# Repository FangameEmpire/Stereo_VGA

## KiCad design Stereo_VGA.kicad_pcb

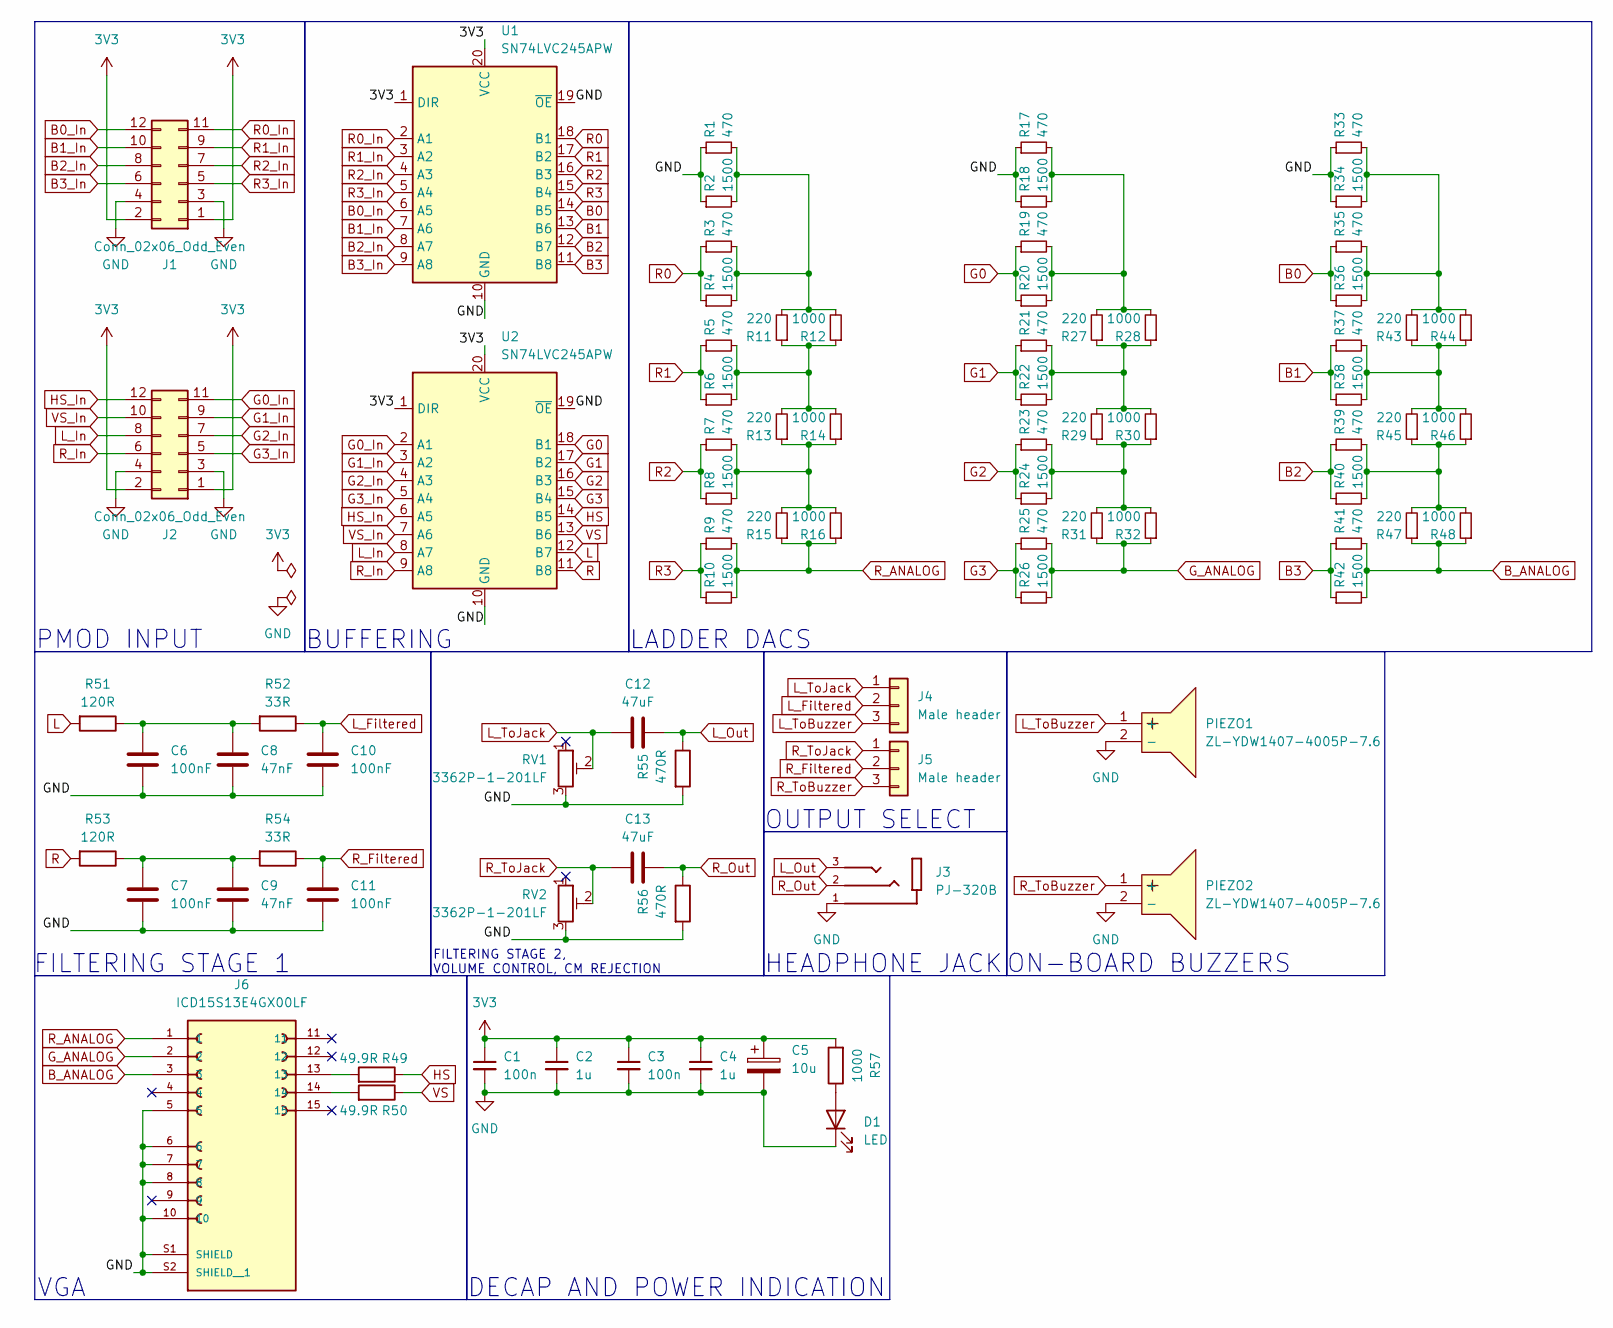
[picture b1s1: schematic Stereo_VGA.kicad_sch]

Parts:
C1, C3: 100n; C_0603_1608Metric; MPN CGA3E3X7S2A104M080AB
C2, C4: 1u; C_0603_1608Metric; MPN CGA3E3X7S2A104M080AB
C5: 10u; CP_Radial_D5.0mm_P2.50mm
C6, C7, C10, C11: 100nF; C_0603_1608Metric; LCSC Part C14663
C8, C9: 47nF; C_0603_1608Metric; LCSC Part C1622
C12, C13: 47uF; C_0603_1608Metric; LCSC Part C16780
D1: LED; LED_0603_1608Metric
J1, J2: Conn_02x06_Odd_Even; PinHeader_2x06_P2.54mm_Horizontal
J3: PJ-320B; BOOMELE_PJ-320B; LCSC Part C2884998
J4, J5: Male header; PinHeader_1x03_P2.54mm_Vertical; LCSC Part C49257
J6: ICD15S13E4GX00LF; AMPHENOL_ICD15S13E4GX00LF; PARTREV G
PIEZO1, PIEZO2: ZL-YDW1407-4005P-7.6; BUZ-TH_BD14.0-P7.60-D0.7-FD; LCSC Part C219740
R1, R3, R5, R7, R9, R17, R19, R21, R23, R25, R33, R35, R37, R39, R41: 470; R_0402_1005Metric; MPN RCC04021K50FKED
R2, R4, R6, R8, R10, R18, R20, R22, R24, R26, R34, R36, R38, R40, R42: 1500; R_0402_1005Metric; MPN RCC04021K50FKED
R11, R13, R15, R27, R29, R31, R43, R45, R47: 220; R_0402_1005Metric; MPN RCC04021K50FKED
R12, R14, R16, R28, R30, R32, R44, R46, R48: 1000; R_0402_1005Metric; MPN RCC04021K50FKED
R49, R50: 49.9R; R_0402_1005Metric; MPN ERJ-2RKF49R9X
R51, R53: 120R; R_0603_1608Metric; LCSC Part C22787
R52, R54: 33R; R_0603_1608Metric; LCSC Part C23140
R55, R56: 470R; R_0603_1608Metric; LCSC Part C23179
R57: 1000; R_0603_1608Metric; LCSC Part C23140
RV1, RV2: 3362P-1-201LF; TRIM_3362P-1-102; LCSC Part C124581
U1, U2: SN74LVC245APW; TSSOP-20_4.4x6.5mm_P0.65mm

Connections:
3V3: C1.1, C2.1, C3.1, C4.1, C5.1, J1.1, J1.2, J2.1, J2.2, R57.2, U1.1 (DIR), U1.20 (VCC), U2.1 (DIR), U2.20 (VCC)
B0: R35.1, R36.1, U1.14 (B5)
B0_In: J1.12, U1.6 (A5)
B1: R37.1, R38.1, U1.13 (B6)
B1_In: J1.10, U1.7 (A6)
B2: R39.1, R40.1, U1.12 (B7)
B2_In: J1.8, U1.8 (A7)
B3: R41.1, R42.1, U1.11 (B8)
B3_In: J1.6, U1.9 (A8)
B_ANALOG: J6.3, R41.2, R42.2, R47.1, R48.1
G0: R19.1, R20.1, U2.18 (B1)
G0_In: J2.11, U2.2 (A1)
G1: R21.1, R22.1, U2.17 (B2)
G1_In: J2.9, U2.3 (A2)
G2: R23.1, R24.1, U2.16 (B3)
G2_In: J2.7, U2.4 (A3)
G3: R25.1, R26.1, U2.15 (B4)
G3_In: J2.5, U2.5 (A4)
GND: C1.2, C2.2, C3.2, C4.2, C5.2, C6.2, C7.2, C8.2, C9.2, C10.2, C11.2, D1.1 (K), J1.3, J1.4, J2.3, J2.4, J3.1, J6.5, J6.6, J6.7, J6.8, J6.10, J6.S1 (SHIELD), J6.S2 (SHIELD__1), PIEZO1.2 (-), PIEZO2.2 (-), R1.1, R2.1, R17.1, R18.1, R33.1, R34.1, R55.2, R56.2, RV1.3, RV2.3, U1.10 (GND), U1.19 (~OE), U2.10 (GND), U2.19 (~OE)
G_ANALOG: J6.2, R25.2, R26.2, R31.1, R32.1
HS: R49.1, U2.14 (B5)
HS_In: J2.12, U2.6 (A5)
L: R51.2, U2.12 (B7)
L_Filtered: C10.1, J4.2, R52.1
L_In: J2.8, U2.8 (A7)
L_Out: C12.1, J3.3, R55.1
L_ToBuzzer: J4.3, PIEZO1.1 (+)
L_ToJack: C12.2, J4.1, RV1.2
unnamed: C6.1, C8.1, R51.1, R52.2
unnamed: C7.1, C9.1, R53.1, R54.2
unnamed: D1.2 (A), R57.1
unnamed: J6.13, R49.2
unnamed: J6.14, R50.2
unnamed: R1.2, R2.2, R3.2, R4.2, R11.2, R12.2
unnamed: R5.2, R6.2, R11.1, R12.1, R13.2, R14.2
unnamed: R7.2, R8.2, R13.1, R14.1, R15.2, R16.2
unnamed: R17.2, R18.2, R19.2, R20.2, R27.2, R28.2
unnamed: R21.2, R22.2, R27.1, R28.1, R29.2, R30.2
unnamed: R23.2, R24.2, R29.1, R30.1, R31.2, R32.2
unnamed: R33.2, R34.2, R35.2, R36.2, R43.2, R44.2
unnamed: R37.2, R38.2, R43.1, R44.1, R45.2, R46.2
unnamed: R39.2, R40.2, R45.1, R46.1, R47.2, R48.2
R: R53.2, U2.11 (B8)
R0: R3.1, R4.1, U1.18 (B1)
R0_In: J1.11, U1.2 (A1)
R1: R5.1, R6.1, U1.17 (B2)
R1_In: J1.9, U1.3 (A2)
R2: R7.1, R8.1, U1.16 (B3)
R2_In: J1.7, U1.4 (A3)
R3: R9.1, R10.1, U1.15 (B4)
R3_In: J1.5, U1.5 (A4)
R_ANALOG: J6.1, R9.2, R10.2, R15.1, R16.1
R_Filtered: C11.1, J5.2, R54.1
R_In: J2.6, U2.9 (A8)
R_Out: C13.1, J3.2, R56.1
R_ToBuzzer: J5.3, PIEZO2.1 (+)
R_ToJack: C13.2, J5.1, RV2.2
VS: R50.1, U2.13 (B6)
VS_In: J2.10, U2.7 (A6)

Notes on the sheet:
BUFFERING
PMOD INPUT
LADDER DACS
FILTERING STAGE 2, VOLUME CONTROL, CM REJECTION
DECAP AND POWER INDICATION
HEADPHONE JACK
OUTPUT SELECT
VGA
ON-BOARD BUZZERS
FILTERING STAGE 1

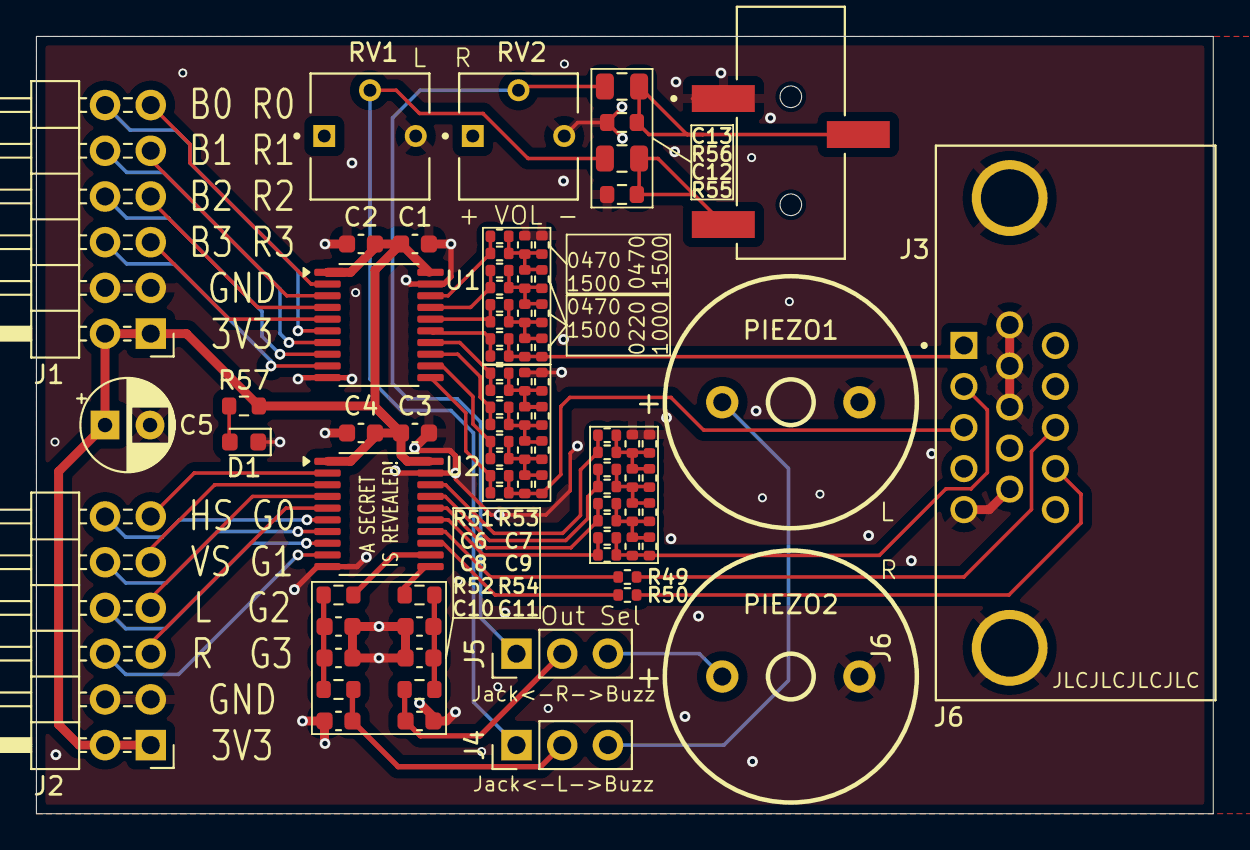
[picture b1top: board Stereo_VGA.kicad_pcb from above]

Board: 2 copper layers, 65.4 x 43.2 mm, 84 parts (1 on the bottom side), 59 nets.

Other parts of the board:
LOGO1: PMOD_LOGO; TT_PMOD_Logo_7mm

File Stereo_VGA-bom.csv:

Comment,Designator,Footprint,LCSC
100 nF,"C1,C3,C6,C7,C10,C11",C_0603_1608Metric,
1 uF,"C2,C4",C_0603_1608Metric,
47 nF,"C8,C9",C_0603_1608Metric,
47 uF,"C12,C13",C_0805_2012Metric,
LED,D1,LED_0603_1608Metric,
Audio,J3,BOOMELE_PJ-320B,C22355831
220R,"R11,R13,R15,R27,R29,R31,R43,R45,R47",R_0402_1005Metric,C25091
470R,"R1,R3,R5,R7,R9,R17,R19,R21,R23,R25,R33,R35,R37,R39,R41",R_0402_1005Metric,C25117
1000R,"R12,R14,R16,R28,R30,R32,R44,R46,R48",R_0402_1005Metric,C11702
1500R,"R2,R4,R6,R8,R10,R18,R20,R22,R24,R26,R34,R36,R38,R40,R42",R_0402_1005Metric,C25867
49.9R,"R49,R50",R_0402_1005Metric,C25120
120R,"R51,R53",R_0603_1608Metric,
470R,"R55,R56",R_0603_1608Metric,
33R,"R52,R54",R_0603_1608Metric,
1000R,R57,R_0603_1608Metric,
SN74LVC245APW,"U1,U2",TSSOP-20_4.4x6.5mm_P0.65mm,
200RV,"RV1,RV2",ZL-YDW1407-4005P-7.6,TRIM_3362P-1-102
Buzzer,"PIEZO1,PIEZO2",ZL-YDW1407-4005P-7.6,BUZ-TH_BD14.0-P7.60-D0.7-FD

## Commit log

2026-02-20 Fix URL
